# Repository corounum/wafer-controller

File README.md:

View this project on [CADLAB.io](https://cadlab.io/node/986). 

# wafer-controller
The controller wafer for the sensestack.

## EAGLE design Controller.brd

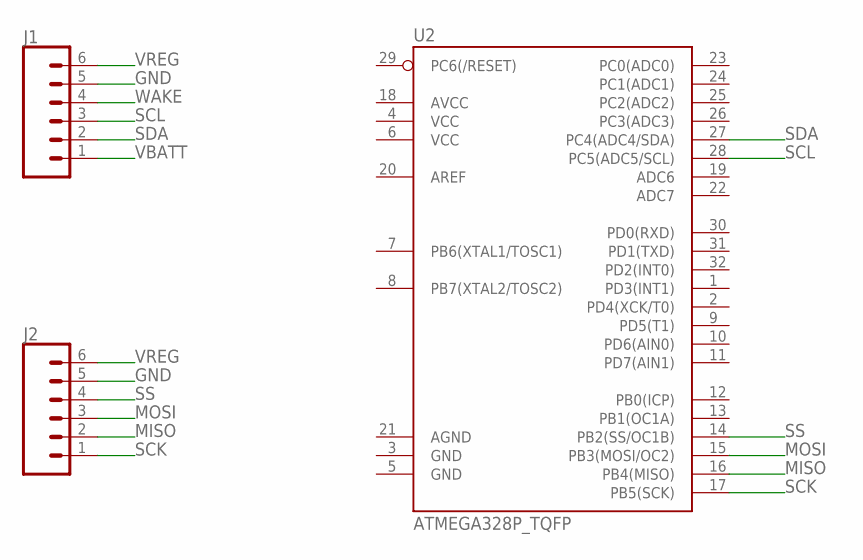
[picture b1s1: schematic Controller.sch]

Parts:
J1, J2: CONN_06LOCK_LONGPADS; 1X06_LOCK_LONGPADS
U2: ATMEGA328P_TQFP; TQFP32-08

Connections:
GND: J1.5, J2.5
MISO: J2.2, U2.16 (PB4(MISO))
MOSI: J2.3, U2.15 (PB3(MOSI/OC2))
SCK: J2.1, U2.17 (PB5(SCK))
SCL: J1.3, U2.28 (PC5(ADC5/SCL))
SDA: J1.2, U2.27 (PC4(ADC4/SDA))
SS: J2.4, U2.14 (PB2(SS/OC1B))
VBATT: J1.1
VREG: J1.6, J2.6
WAKE: J1.4

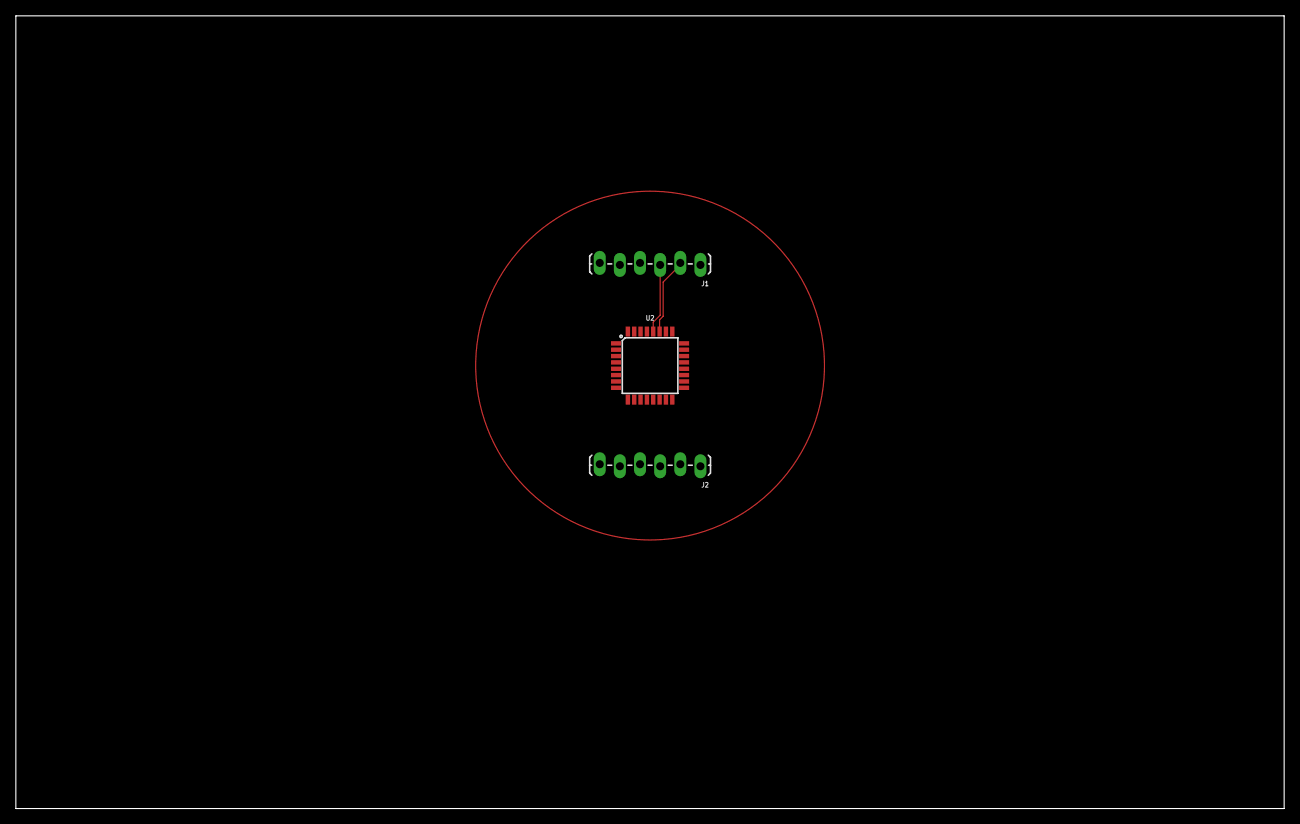
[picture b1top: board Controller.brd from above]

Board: 2 copper layers, 160.0 x 100.0 mm, 3 parts (0 on the bottom side), 8 nets.

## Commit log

2018-05-05 Backlink to CADLAB.io has been added.
2018-05-05 Adding in start of board.

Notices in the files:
parts and their libraries:
SparkFun-Connectors: Licensing: Creative Commons ShareAlike 4.0 International - https://creativecommons.org/licenses/by-sa/4.0
